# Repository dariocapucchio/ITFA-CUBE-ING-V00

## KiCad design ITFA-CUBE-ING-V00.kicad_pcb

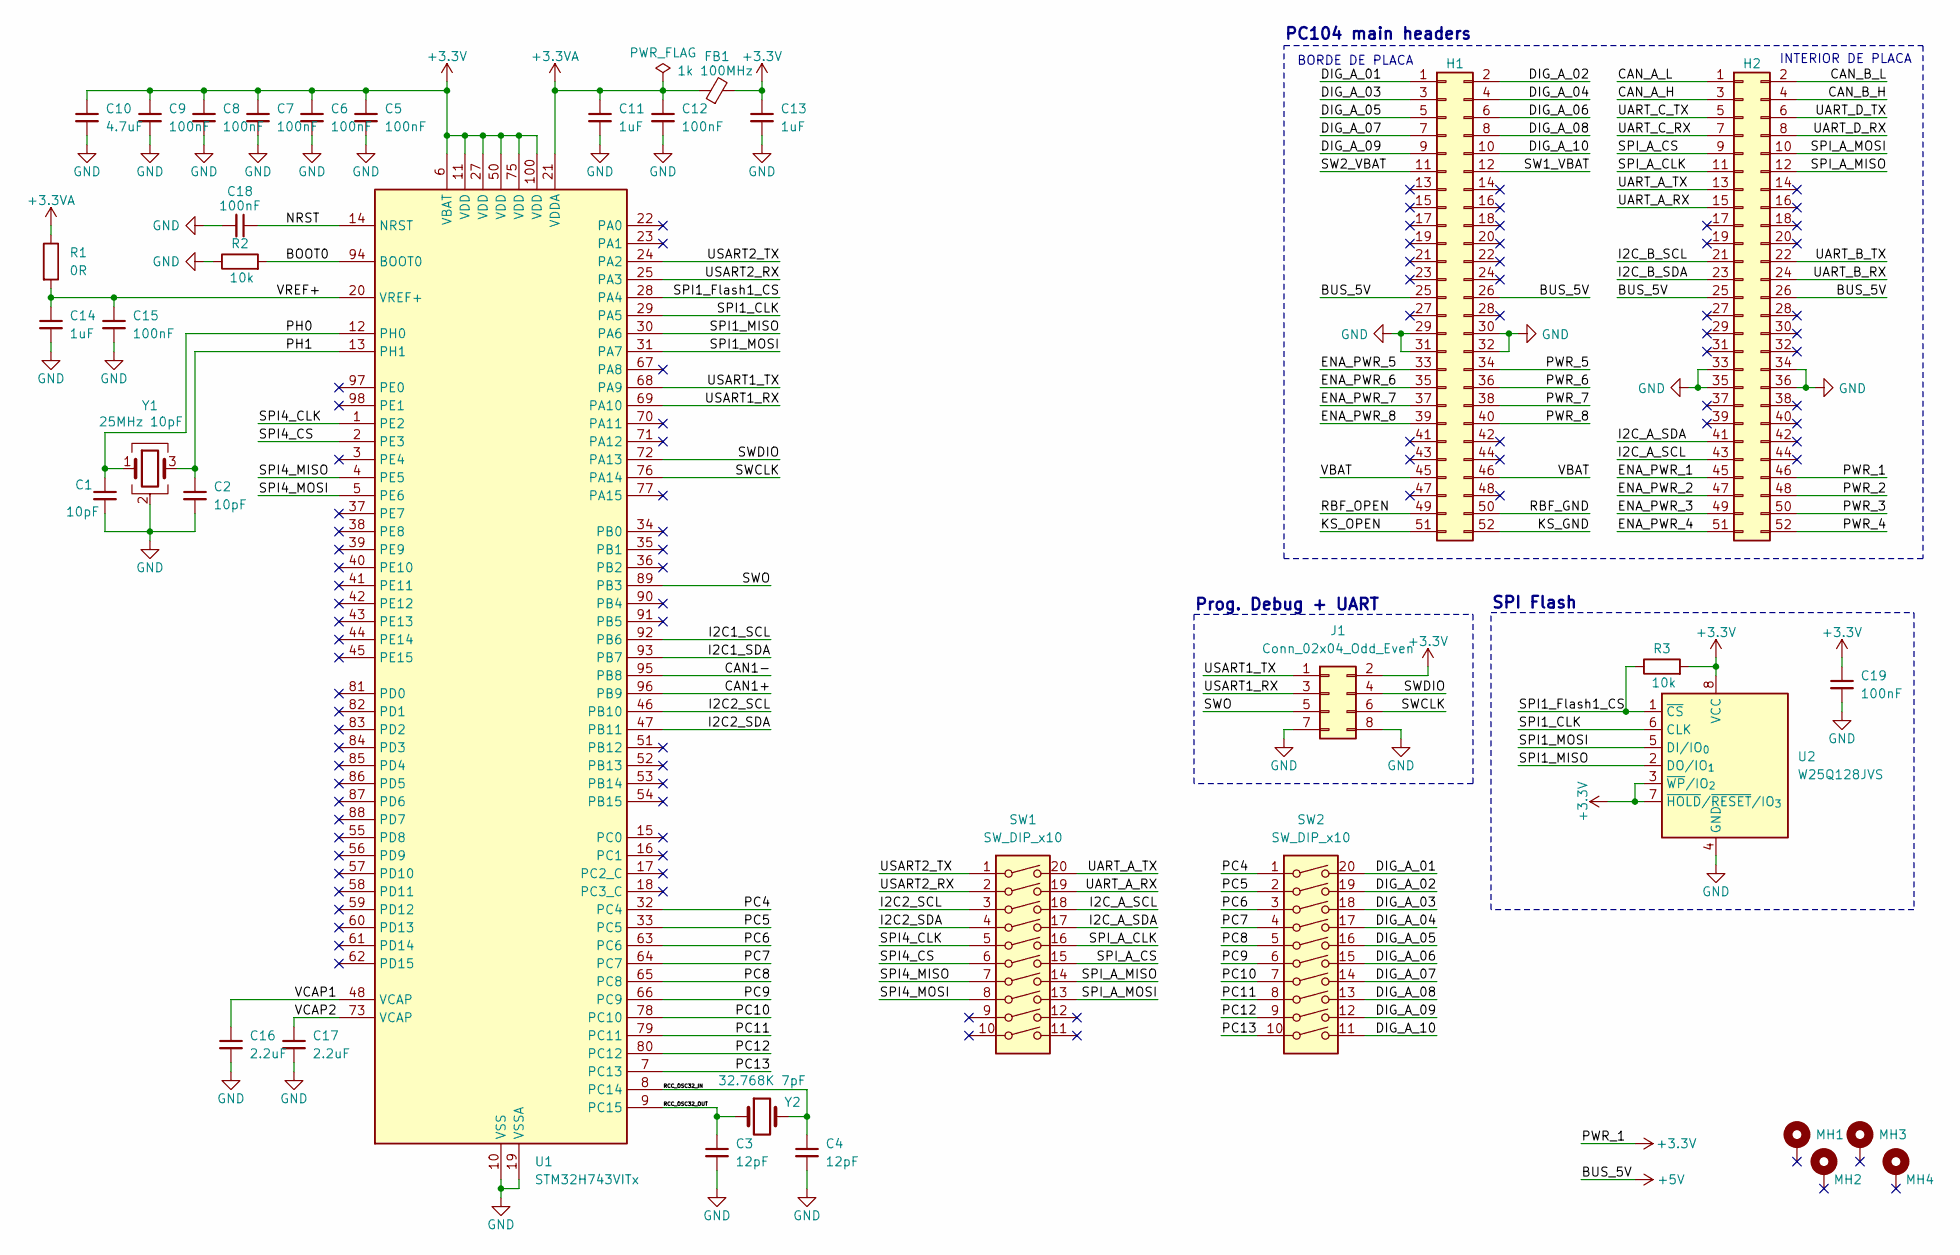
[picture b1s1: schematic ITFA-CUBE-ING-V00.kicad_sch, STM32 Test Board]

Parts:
C1, C2: 10pF; C_0402_1005Metric
C3, C4: 12pF; C_0402_1005Metric
C5, C6, C7, C8, C9, C12, C15, C18, C19: 100nF; C_0603_1608Metric
C10: 4.7uF; C_0603_1608Metric
C11, C13, C14: 1uF; C_0603_1608Metric
C16, C17: 2.2uF; C_0603_1608Metric
FB1: 1k 100MHz; L_0805_2012Metric
H1, H2: Conn_02x26_Odd_Even; PinSocket_2x26_P2.54mm_Vertical
J1: Conn_02x04_Odd_Even; PinHeader_2x04_P2.54mm_Horizontal
MH1, MH2, MH3, MH4: MountingHole_Pad; MountingHole_3.2mm_M3_Pad_Via
R1: 0R; R_0603_1608Metric
R2, R3: 10k; R_0603_1608Metric
SW1, SW2: SW_DIP_x10
U1: STM32H743VITx; LQFP-100_14x14mm_P0.5mm
U2: W25Q128JVS; SOIC-8_5.3x5.3mm_P1.27mm
Y1: 25MHz 10pF; Crystal_SMD_3225-4Pin_3.2x2.5mm
Y2: 32.768K 7pF; Crystal_SMD_3215-2Pin_3.2x1.5mm

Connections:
+3.3V: C5.1, C6.1, C7.1, C8.1, C9.1, C10.1, C13.1, C19.1, FB1.2, H2.46, J1.2, R3.2, U1.6 (VBAT), U1.11 (VDD), U1.27 (VDD), U1.50 (VDD), U1.75 (VDD), U1.100 (VDD), U2.3 (~WP/IO_{2}), U2.7 (~HOLD/~RESET/IO_{3}), U2.8 (VCC)
+3.3VA: C11.1, C12.1, FB1.1, R1.1, U1.21 (VDDA)
+5V: H1.25, H1.26, H2.25, H2.26
/BOOT0: R2.2, U1.94 (BOOT0)
/CAN1+: U1.96 (PB9)
/CAN1-: U1.95 (PB8)
/CAN_A_H: H2.3
/CAN_A_L: H2.1
/CAN_B_H: H2.4
/CAN_B_L: H2.2
/DIG_A_01: H1.1, SW2.20
/DIG_A_02: H1.2, SW2.19
/DIG_A_03: H1.3, SW2.18
/DIG_A_04: H1.4, SW2.17
/DIG_A_05: H1.5, SW2.16
/DIG_A_06: H1.6, SW2.15
/DIG_A_07: H1.7, SW2.14
/DIG_A_08: H1.8, SW2.13
/DIG_A_09: H1.9, SW2.12
/DIG_A_10: H1.10, SW2.11
/ENA_PWR_1: H2.45
/ENA_PWR_2: H2.47
/ENA_PWR_3: H2.49
/ENA_PWR_4: H2.51
/ENA_PWR_5: H1.33
/ENA_PWR_6: H1.35
/ENA_PWR_7: H1.37
/ENA_PWR_8: H1.39
/I2C1_SCL: U1.92 (PB6)
/I2C1_SDA: U1.93 (PB7)
/I2C2_SCL: SW1.3, U1.46 (PB10)
/I2C2_SDA: SW1.4, U1.47 (PB11)
/I2C_A_SCL: H2.43, SW1.18
/I2C_A_SDA: H2.41, SW1.17
/I2C_B_SCL: H2.21
/I2C_B_SDA: H2.23
/KS_GND: H1.52
/KS_OPEN: H1.51
/NRST: C18.1, U1.14 (NRST)
/PC4: SW2.1, U1.32 (PC4)
/PC5: SW2.2, U1.33 (PC5)
/PC6: SW2.3, U1.63 (PC6)
/PC7: SW2.4, U1.64 (PC7)
/PC8: SW2.5, U1.65 (PC8)
/PC9: SW2.6, U1.66 (PC9)
/PC10: SW2.7, U1.78 (PC10)
/PC11: SW2.8, U1.79 (PC11)
/PC12: SW2.9, U1.80 (PC12)
/PC13: SW2.10, U1.7 (PC13)
/PH0: C1.1, U1.12 (PH0), Y1.1
/PH1: C2.1, U1.13 (PH1), Y1.3
/PWR_2: H2.48
/PWR_3: H2.50
/PWR_4: H2.52
/PWR_5: H1.34
/PWR_6: H1.36
/PWR_7: H1.38
/PWR_8: H1.40
/RBF_GND: H1.50
/RBF_OPEN: H1.49
/RCC_OSC32_IN: C4.1, U1.8 (PC14), Y2.2
/RCC_OSC32_OUT: C3.1, U1.9 (PC15), Y2.1
/SPI1_CLK: U1.29 (PA5), U2.6 (CLK)
/SPI1_Flash1_CS: R3.1, U1.28 (PA4), U2.1 (~CS)
/SPI1_MISO: U1.30 (PA6), U2.2 (DO/IO_{1})
/SPI1_MOSI: U1.31 (PA7), U2.5 (DI/IO_{0})
/SPI4_CLK: SW1.5, U1.1 (PE2)
/SPI4_CS: SW1.6, U1.2 (PE3)
/SPI4_MISO: SW1.7, U1.4 (PE5)
/SPI4_MOSI: SW1.8, U1.5 (PE6)
/SPI_A_CLK: H2.11, SW1.16
/SPI_A_CS: H2.9, SW1.15
/SPI_A_MISO: H2.12, SW1.14
/SPI_A_MOSI: H2.10, SW1.13
/SW1_VBAT: H1.12
/SW2_VBAT: H1.11
/SWCLK: J1.6, U1.76 (PA14)
/SWDIO: J1.4, U1.72 (PA13)
/SWO: J1.5, U1.89 (PB3)
/UART_A_RX: H2.15, SW1.19
/UART_A_TX: H2.13, SW1.20
/UART_B_RX: H2.24
/UART_B_TX: H2.22
/UART_C_RX: H2.7
/UART_C_TX: H2.5
/UART_D_RX: H2.8
/UART_D_TX: H2.6
/USART1_RX: J1.3, U1.69 (PA10)
/USART1_TX: J1.1, U1.68 (PA9)
/USART2_RX: SW1.2, U1.25 (PA3)
/USART2_TX: SW1.1, U1.24 (PA2)
/VBAT: H1.45, H1.46
/VCAP1: C16.1, U1.48 (VCAP)
/VCAP2: C17.1, U1.73 (VCAP)
/VREF+: C14.1, C15.1, R1.2, U1.20 (VREF+)
GND: C1.2, C2.2, C3.2, C4.2, C5.2, C6.2, C7.2, C8.2, C9.2, C10.2, C11.2, C12.2, C13.2, C14.2, C15.2, C16.2, C17.2, C18.2, C19.2, H1.29, H1.30, H1.31, H1.32, H2.33, H2.34, H2.35, H2.36, J1.7, J1.8, R2.1, U1.10 (VSS), U1.19 (VSSA), U1.26 (VSS), U1.49 (VSS), U1.74 (VSS), U1.99 (VSS), U2.4 (GND), Y1.2 (G), Y1.4 (G)

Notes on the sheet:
Prog. Debug + UART
BORDE DE PLACA
PC104 main headers
INTERIOR DE PLACA
SPI Flash

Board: 2 copper layers, 34 parts (0 on the bottom side), 23 nets, no tracks yet.

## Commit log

2026-04-29 Primer commit
2026-05-04 Avance uc
2026-05-04 Actualizandon esquematico
